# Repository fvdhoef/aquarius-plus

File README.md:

**Next-generation Z80-based retro computer system**

## Documentation

For documentation, please take a look at the [Wiki](https://github.com/fvdhoef/aquarius-plus/wiki).

## Abstract:

What would the Aquarius have evolved into if Mattel hadn't abandoned the system back in 1984? The Aquarius+ is the next-generation of Z80-based 8-bit hardware for the Aquarius platform. The intent is to deliver a cost-effective, backwards-compatible retro computer system that both developers and nostalgists will love and use, all in the spirit of the original, orphaned Aquarius platform.

## Features:

- Backward compatibility with existing Aquarius hardware and software
- Modern, flexible video solution that supports bitmapped graphics, sprites, and tiles, delivered through clean VGA output
- Dual AY sound chips (virtual) for six sound voices
- 512kb of paged RAM in four 16k banks
- Reworked SYSROM and programmable CHARROM
- Integrated SD card and commands (remove dependency on cassette loading)
- WiFi connectivity
- Bluetooth connectivity for modern game controllers

## Folder structure

| Directory           | Description                                                                                                                                                                     |
| ------------------- | ------------------------------------------------------------------------------------------------------------------------------------------------------------------------------- |
| [EndUser](EndUser/) | These files are meant for the normal end-user, that just wants to play and work with the system. You can find some nice sample programs, games and music to run on system here. |
| [Maker](Maker/)     | Files required for makers to manufacture and assemble an Aquarius+ system.                                                                                                      |
| [SDK](SDK/)         | If you want to develop your own software for the Aquarius+, look here.                                                                                                          |
| [System](System/)   | This contains all other files related to the system, including: Schematics/PCB, FPGA, ESP32, Emulator                                                                           |

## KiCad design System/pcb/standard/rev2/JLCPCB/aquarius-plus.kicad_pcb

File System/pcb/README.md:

# Aquarius<sup>+</sup> PCBs
Development of PCBs (Printed Circuit Boards) for the **Aquarius<sup>+</sup>** platform

## Introduction
The **Aquarius<sup>+</sup>** was developed as an open-source platform, including the hardware that comprises the system. To accomplish this and to make tools for the development and manufacture of the platform as accessible as possible, [KiCAD](https://github.com/KiCad/kicad-source-mirror) is used for PCB development, as it is a free, open source tool that has anyone can learn and use.

## Releases
Releases from this repo are by model/PCB and are geared specifically for manufacturing rather than PCB development.

> For example, if you want to make your own **Aquarius<sup>+</sup> Mini**, you would go to the [**Releases**](https://github.com/1stage/aquarius-plus-pcbs/releases) section, find the newest release for an **Aquarius<sup>+</sup> Mini**, and download it.

The **Source code (zip)** or **Source code (tar.gz)** payload will consist of the following components:
 * Gerber files, compressed in ZIP format (includes PCB, Drill, and Map files)
 * PDFs of the SCHEMATIC and PCB
 * BOM (Bill of Materials) and CPL1 (Component Placement Layout) files in XLSX (MS Excel) format, organized for JLCPCB manufacturing.
 * Release notes and other instructions in TXT format

## Development
If you want to explore how the **Aquarius<sup>+</sup>** is designed using KiCAD, you will need to Clone or Fork this repo to your local system. From there you can review and experiment with the schematic, PCB, and other files within the KiCAD environment.

****

## PCB Manufacturing

### PCB Terms
 - BOM - Bill of Materials
 - CPL - Component Placement Layout/List (sometimes referred to as CPL1)
 - PCB - Printed Circuit Board
 - SMT - Surface mount (sometimes referred to as SMD)
 - THT - Through hole

### Process
This guide assumes that the maker will be having a third-party manufacturer create and assemble the PCB. It does not cover user-manufactered PCBs or assembly using a reflow oven or other manual tasks.

#### **JLCPCB** (Cheapest)
1. **Order the parts**
    - On the [JLCPCB](https://jlcpcb.com) main site, log in and go to Parts Manager, then Order Parts, then JLCPCB Parts.
    - From the JLCPCB Assembly Parts page, select BOM Tool.
    - Upload the BOM file to the site. From the pop-up, select the number of PCBs you want to manufacture. This multiplies the quantities for you for each item.
    - Add to cart, pay for items, and wait.
    - Over the next several days, you will get email notifications as items arrive into your parts inventory. Sometimes, there will be an increase or decrease in the amount you paid, so JLCPCB will either ask you to pay the difference (part is more expensive than estimated) or they will credit your purchase (part was less expensive than estimated). Acknowledge these messages, pay the difference (as needed), and wait.
    - Once all of the parts are in your inventory, proceed to the next step.
3. **Order the assembled PCB**
    - Log into JLCPCB, and start a new order.
    - Upload the Gerber files.
    - Mark the order as SMT Assembly.
    - Upload the BOM and CPL files.
    - Ensure there are sufficient quantities of the parts you need. If not, go back to [Order the parts](#JLCPCB) section.
    - Review the placement of all parts. Note that some of the items (ESP32, switch) don't have a 3D model to go with their part, so a small 2x2 checkerboard is used. Don't worry about these items. The CPL1 file has been tuned to accurately place the components, so this step is for QA to make sure nothing has gone wrong.
      - If you select a part (blue highlight), you can nudge it with the arrow keys. RIGHT nudges increase the X. LEFT nudges decrease the X. UP nudges increase the Y. DOWN nudges decrease the Y.
      - For THT parts, it's easier to align the parts from the BOTTOM view, but remember that your X axis is now flipped, so a RIGHT nudge decreases the X and a LEFT nudge increases it.
      - Each "nudge" is a difference of 0.0635mm, and can be added or subtracted from the CPL file accordingly... i.e. if you nudge a part UP (increase y axis) five times, you're modifying it 5 x 0.0635mm or 3.175. So if it's value in the CPL file is -45.025, the new value should be -44.7075.
    - JLCPCB will automatically set the "confirm PCB" and "confirm placement" options, and let you know that there will be a small charge for this.
    - Add to cart, pay for items, and wait.
    - You will get at least two emails. The first will be to confirm your PCB file. This is done in your Order History window. Confirm it. The second email will be to confirm the layout of the components. In your Order History window, the lower Confirm Placement button brings a pop-up which shows the placement of the SMT parts (THT or throughhole is done separately). Everything should be fine, but reply to the email and ask to see a 3D of the cartridge port placement. This will take a day or so, but so long as the port is shown in the far right columns of pins, you can confirm placement.
    - Check the progress of your order daily to make sure there's nothing you need to confirm. Once the product has shipped, you can move onto Assembly.

#### **PCBWay** (PROCESS IN DEVELOPMENT)
1. **Order the assembled PCBs**
    - Visit the PCBWay Aquarius+ Shared Project page for the version you want to manufacture.
	    - [Aquarius+ Standard](https://www.pcbway.com/project/shareproject/Aquarius_Computer_Standard_PCB_0087c6b7.html) 
		- Aquarius+ Mini (coming soon)
	- Click on each of the following buttons to download the manufacturing files:
		- BOM(Bill of materials) - AQP_xxx_BOM_PCBWay_PCBWay Community.xlsx
		- Centroid file - AQP_xxx_CPL1_PCBWay_PCBWay Community.xlsx
		- The xxx in these filenames will be either STD or MINI, depending on the version.
	- Select **PCB+Assembly** and click **Add to Cart**
	- On the Order Page, in the PCB Specification Selection area, confirm the following selections (recommended):
		- Quantity (single): 5 pcs (this is the minimum order of PCBs, but they don't all have to be assembled, and you may have spares if not all are assembled)
		- Solder mask: Blue
		- Remove product No.: Yes (extra+$ 1.5)
		- All other defaults are fine
	- Click on the Assembly Service checkbox to expand/activate it, and confirm the following selections (recommended):
		- 3 flexible options: Turnkey
		- Quantity: 1 pcs (1 is the minimum assembled quantity; you can assemble up to 5 pcs without increasing the number of PCBs above)
		- Copy and paste the contents of the "Mfg_Assembly_Notes_PCBWay.txt" file into the Detailed information of assembly: field.
		- All other defaults are fine
	- Save to Cart
	- In the Cart, under the "Assembly for PCB" section, click on the blue Add File icon to add these files to the Assembly order (you downloaded them above:
		- Click the Parts List (BOM) Upload button and attach  AQP_xxx_BOM_PCBWay_PCBWay Community.xlsx
		- Click the Upload Centroid file and attach AQP_xxx_CPL1_PCBWay_PCBWay Community.xlsx
		- The xxx in these filenames will be either STD or MINI, depending on the version.
		- Click Submit Order now button.
	- You will wait up to a day or so for the files to be reviewed and approved, and a Quote issued.
	- Once you've been approved, return to your Cart and click Proceed to Checkout to pay the amount due
	- Over the next day or two, check your email and answer any questions they might have. 
2. **Wait for about 30 days** (seriously).
3. **Approve final assembly**
	- Reply to the email that will be sent for you to visually inspect/approve parts placement for the board(s), approving the continuation of manufacturing.
	- You will receive shipping confirmation after the boards are completed. Note that for larger orders, you MAY have to pay additional import taxes.
4. **Receive and verify PCBs**
	- You should visually inspect the PCBs once you get them. Make sure all parts are properly installed and soldered in place.
	- Continue onto the Assembly section below.

#### Assembling the Aquarius+
 - Make sure your shipment package has no obvious damage. If it does, take pictures before you open the box and save them for later. Most of the time, a ding or puncture will not be a problem, as the contents are typically very well wrapped.
 - There are sometimes small beads or blobs of solder that get deposited on the top of the board. With a magnifier, check ALL components to ensure there are no obvious solder blobs or bridges on the components, both SMT and THT. Now, check the BACK side of the board to ensure all THT components have solid, well-tented solder joints. Check the metal shrouds around the USB, controllers (DB9), VGA, power switch, and SD card socket to remove any accidental blobs or splashes. They should pop free with minimal force.
 - To assist in the SMT mounting process, manufacturers add additional "rails" to the PCB for handling. Using a small pair of needle-nose pliers, carefully remove these rails by bending along the V cut that has been cut into the PCB next to these rails. Be cautious not to damage any components that rest on this rail (LED, SD card socket, etc.). You can use a small file to remove any remaining burrs along these new edges. The rails can be thrown away.
 -  The wave solder that is used for the THT components leaves a sticky residue, as does the flux used for the SMT components. This residue should be cleaned using a two-step process, first with an alcohol-based solvent and a soft-bristle brush (an old toothbrush works great), and second with a mild de-greasing detergent, also agitated with a soft-bristle brush. Clean BOTH sides of the PCB thoroughly, first with the alcohol (I use left-over hand sanitizer from COVID), and then with the detergent (I use Krud Kutter), rinsing with water after each scrub down. Take care around delicate parts: the goal is to remove residue, not PCB components. Afterwards, either allow to air dry for 24 hours, or use a gentle, low-pressure compressed air source to drive the remaining water from all areas of the PCB (ports, power switch, under chips), again, taking care to not damage PCB components.
 - Once PCB has been cleaned and thoroughly dried, it's time to program the initial image for the Aquarius+. You're programming the ESP32 with the image that then gets sent to the Spartan 6 FPGA. From the GitHub, download the newest AquariusPlus-Firmware-xxx.zip bundle, decompress it, and follow the instructions for setting up the ESP software on your system. Using a USB to USB Micro cable and three 0.1" / 2.54mm pitch jumpers, connect the pins at JP1, JP2, and JP3, and plug the cable into the Aquarius+ power port and into your computer. Switch on the Aquarius+ power supply and note which COM port it appears on.

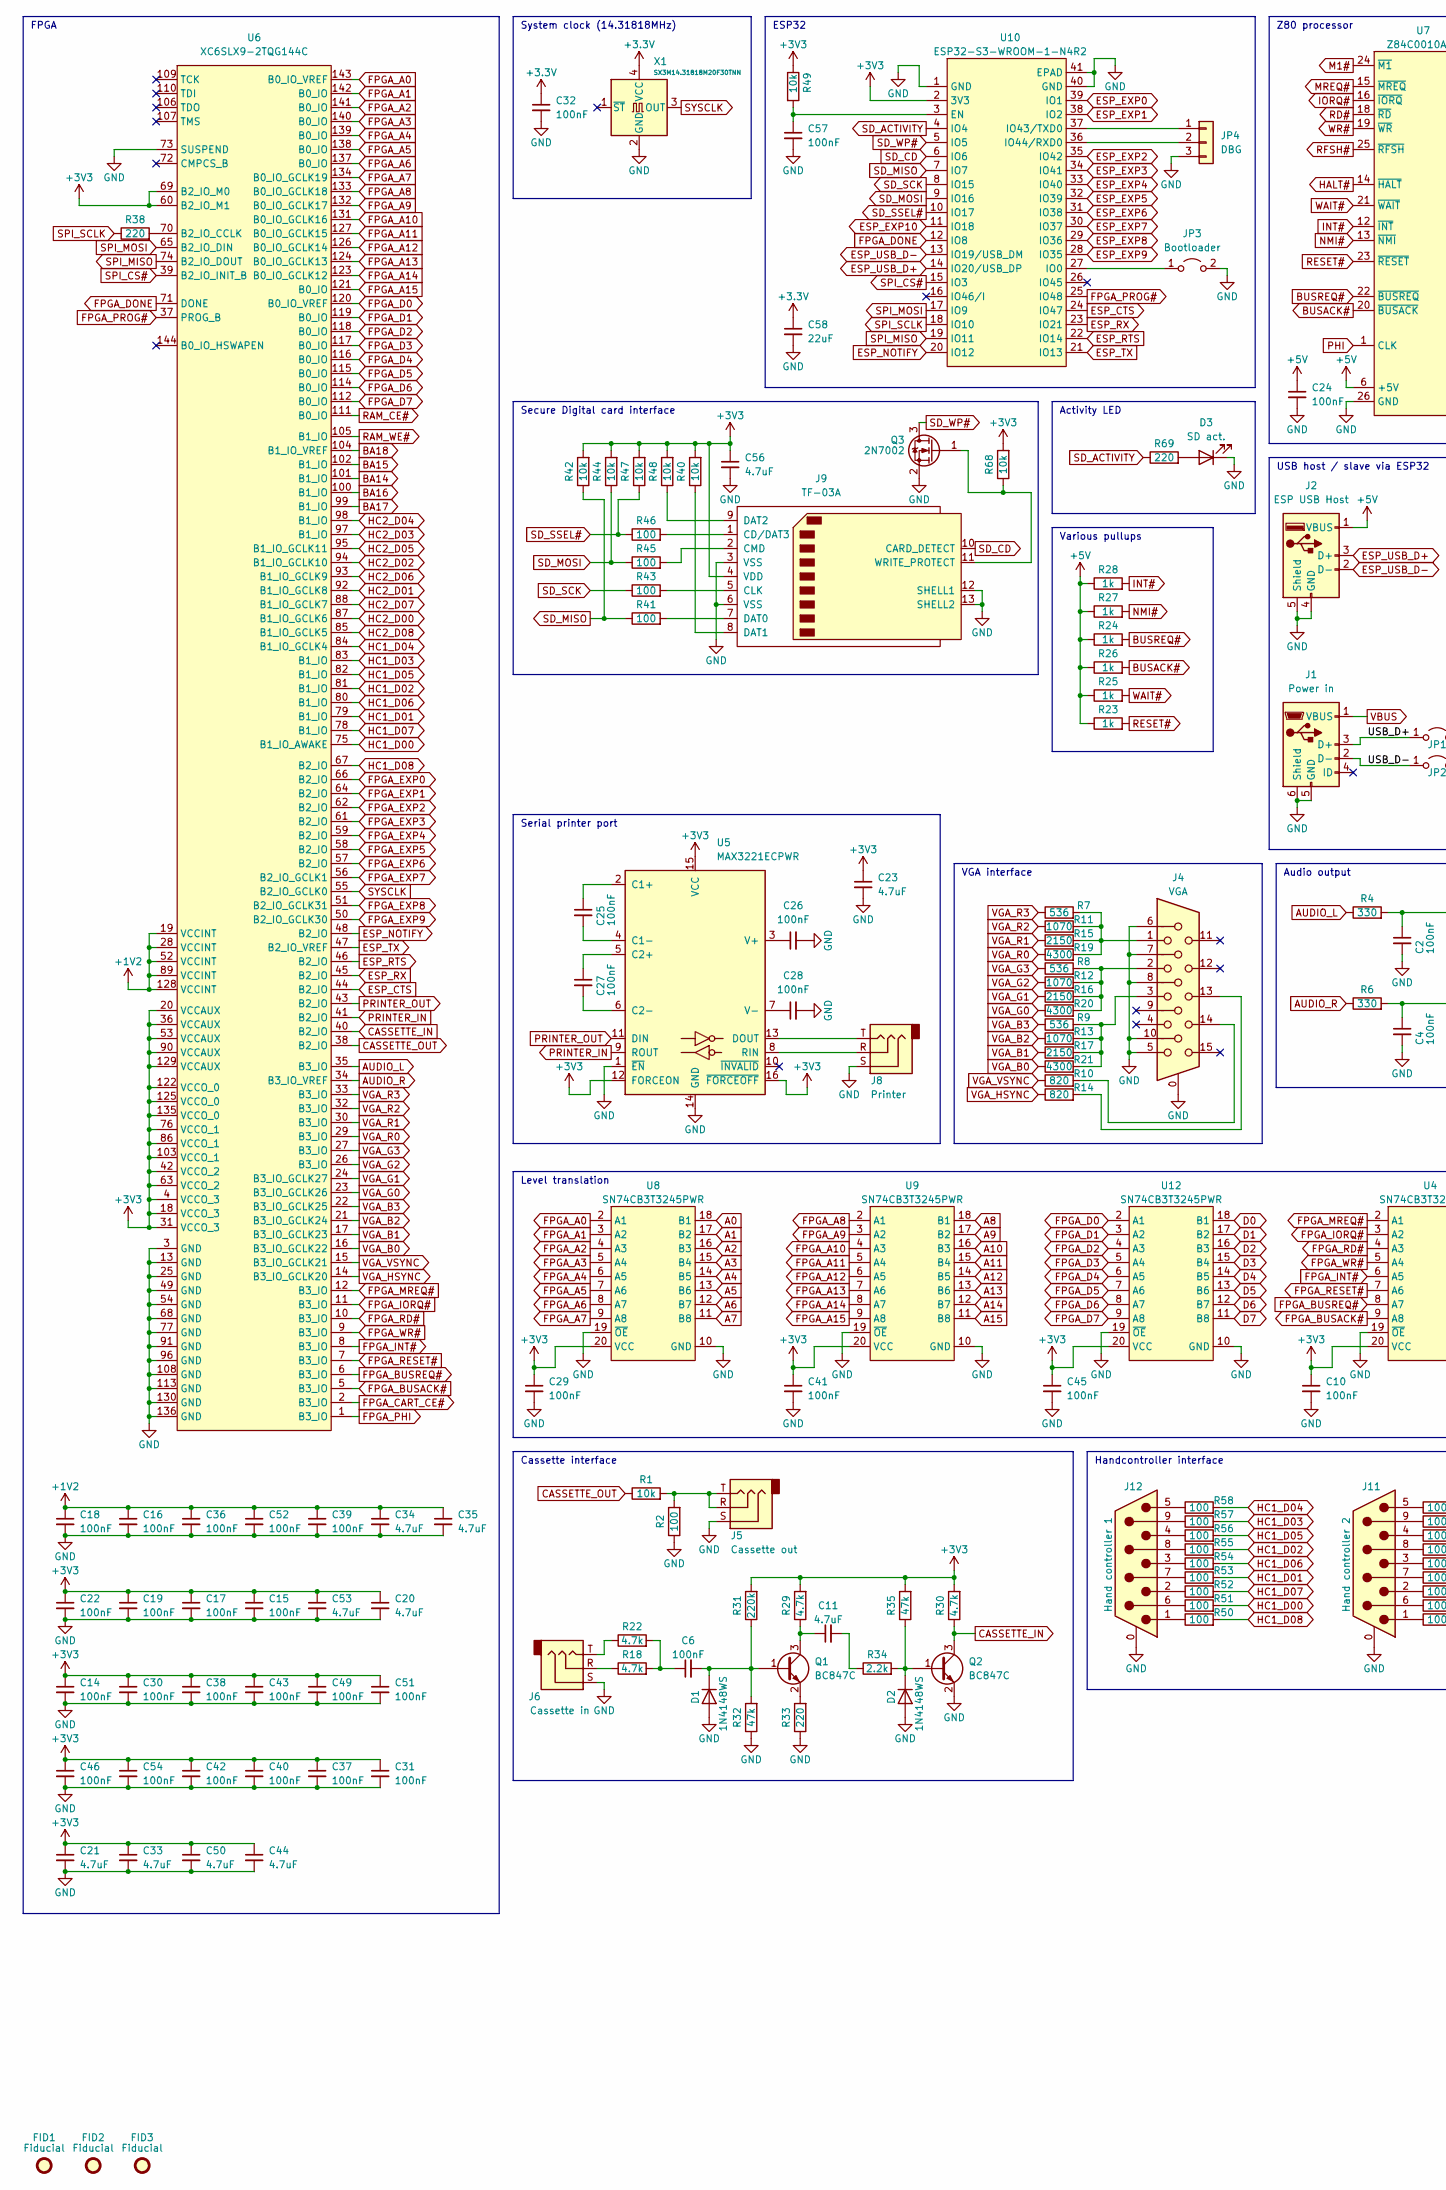
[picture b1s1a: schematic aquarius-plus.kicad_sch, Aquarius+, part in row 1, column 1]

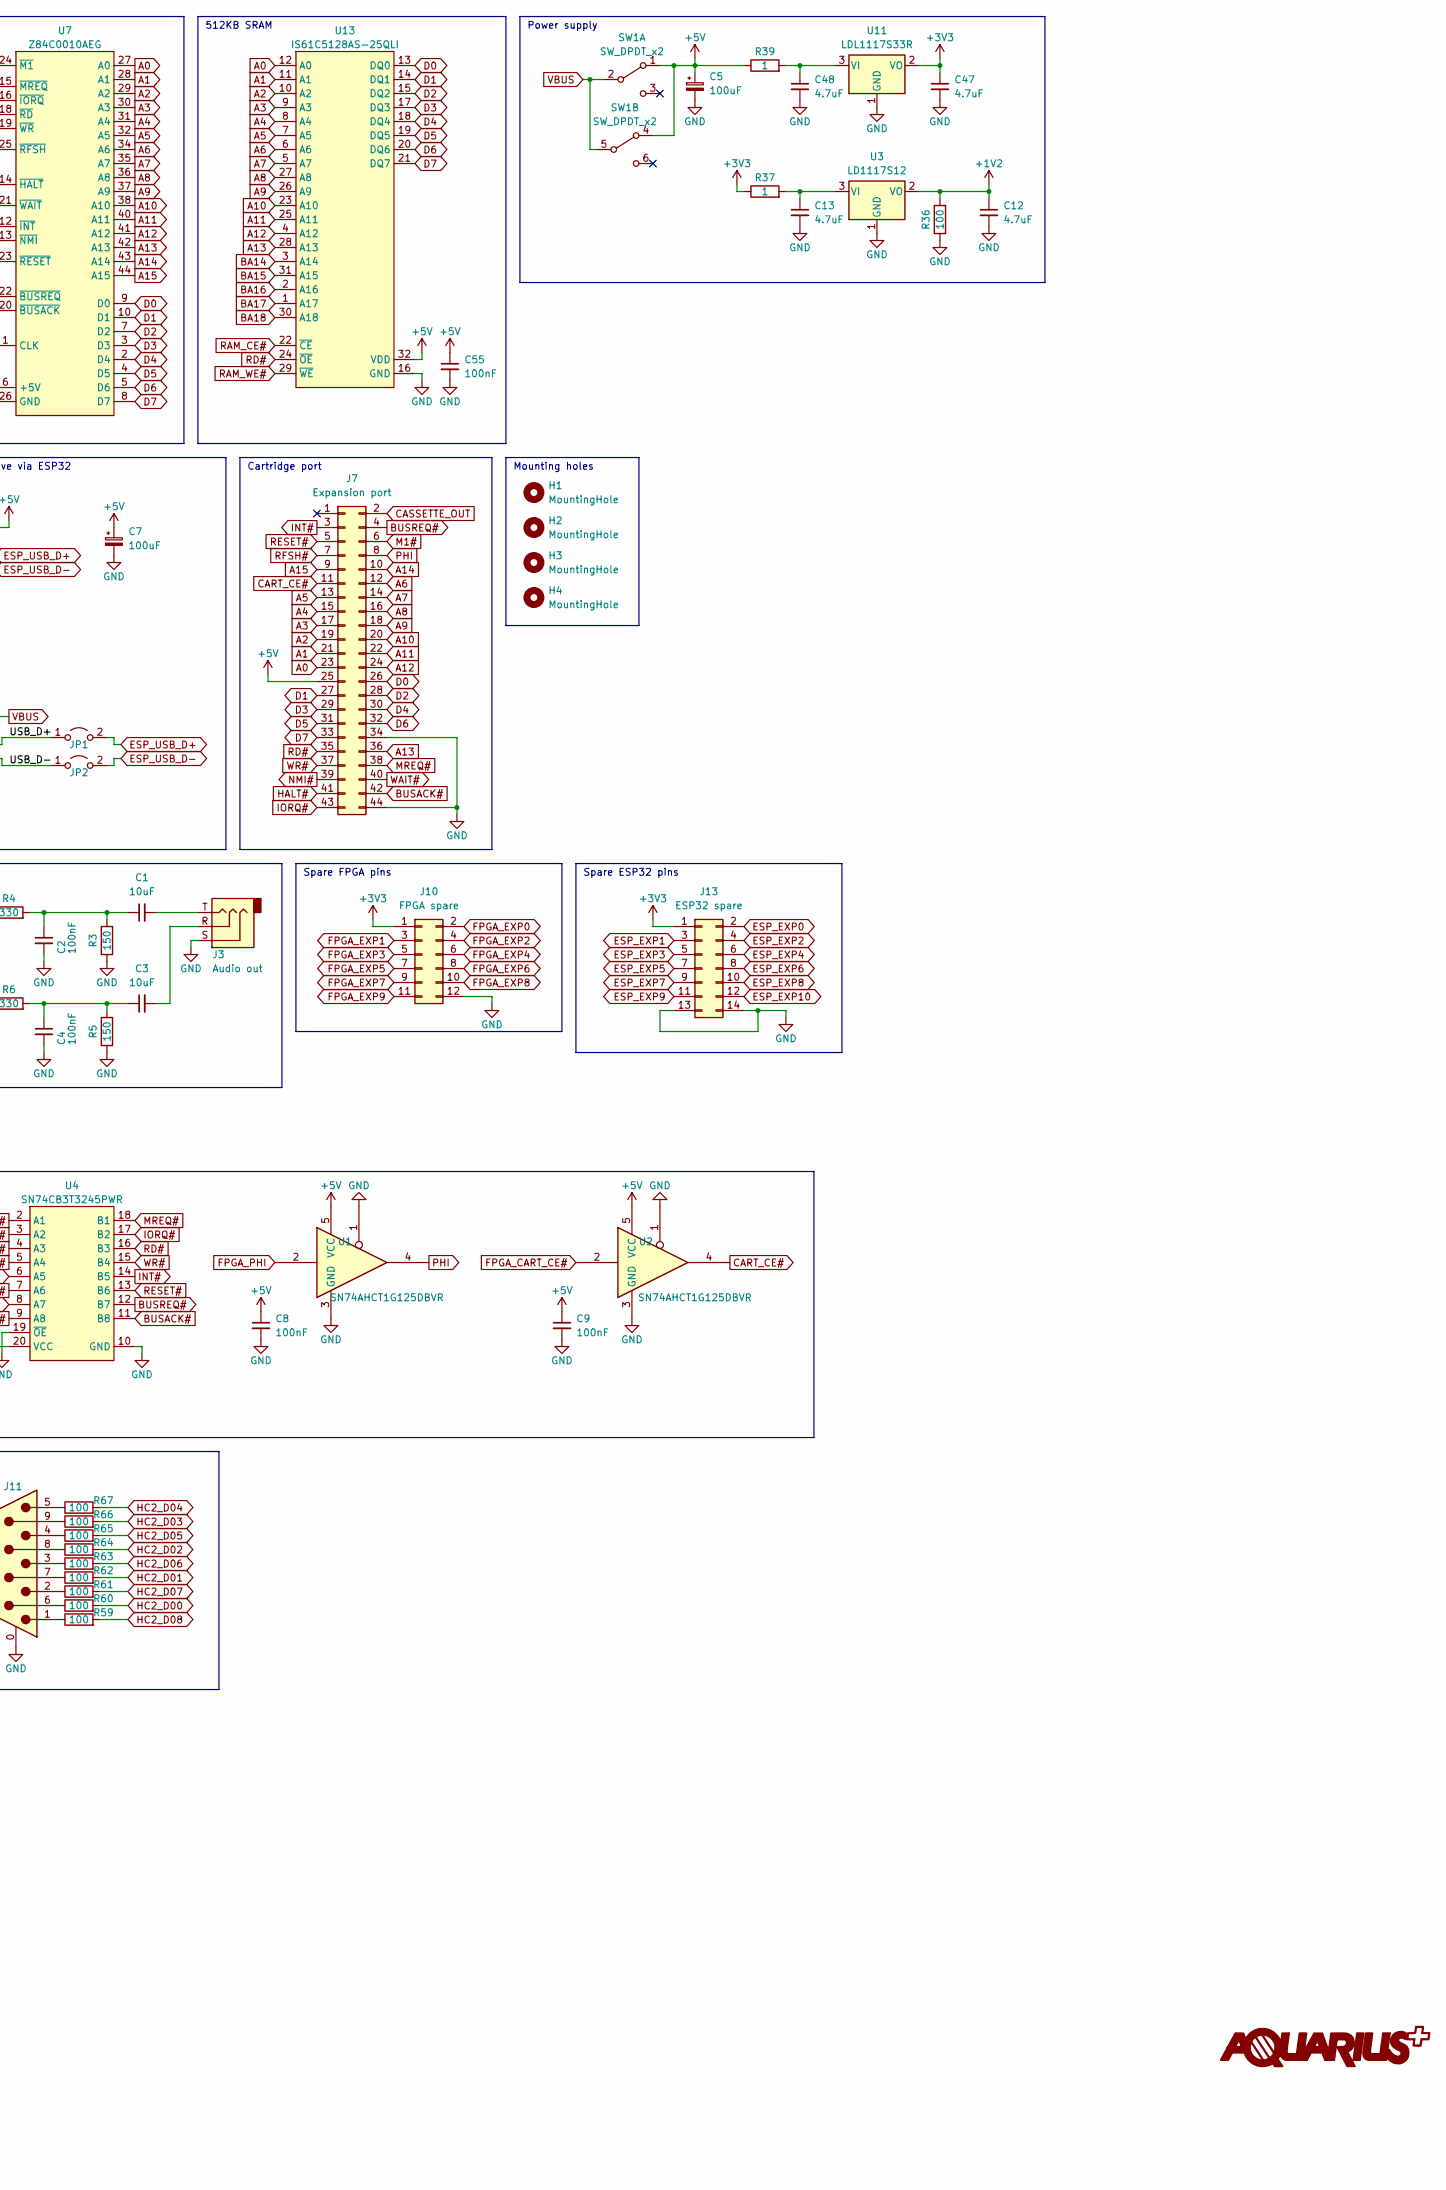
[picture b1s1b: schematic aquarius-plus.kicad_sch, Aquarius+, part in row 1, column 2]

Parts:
C1, C3: 10uF; C_0805_2012Metric
C2, C4, C6, C8, C9, C10, C14, C15, C16, C17, C18, C19, C22, C24, C25, C26, C27, C28, C29, C30, C31, C32, C36, C37, C38, C39, C40, C41, C42, C43, C45, C46, C49, C51, C52, C54, C55, C57: 100nF; C_0603_1608Metric
C5, C7: 100uF; CP_Elec_6.3x7.7
C11, C12, C13, C20, C21, C23, C33, C34, C35, C44, C47, C48, C50, C53, C56: 4.7uF; C_0603_1608Metric
C58: 22uF; C_1206_3216Metric
D1, D2: 1N4148WS; D_SOD-323_HandSoldering
D3: SD act.; LED_D3.0mm_Horizontal_O1.27mm_Z2.0mm
FID1, FID2, FID3: Fiducial; Fiducial_1mm_Mask2mm
H1, H2, H3, H4: MountingHole; MountingHole_3.2mm_M3
J1: Power in; AMPHENOL_10118194-0001LF
J2: ESP USB Host; USB_A_Molex_67643_Horizontal
J3: Audio out; C2939180
J4: VGA; ICD15S13E4GV00LF
J5: Cassette out; C2939180
J6: Cassette in; C2939180
J7: Expansion port; CR22A-44D-2.54DSA(70)
J8: Printer; C2939180
J9: TF-03A
J10: FPGA spare; PinHeader_2x06_P2.54mm_Vertical
J11: Hand controller 2; DSUB-9_Male_Horizontal_P2.77x2.84mm_EdgePinOffset9.90mm_Hou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
J12: Hand controller 1; DSUB-9_Male_Horizontal_P2.77x2.84mm_EdgePinOffset9.90mm_Hou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
J13: ESP32 spare; PinHeader_2x07_P2.54mm_Vertical
JP1, JP2: USB; PinHeader_1x02_P2.54mm_Vertical
JP3: Bootloader; PinHeader_1x02_P2.54mm_Vertical
JP4: DBG; PinHeader_1x03_P2.54mm_Vertical
Q1, Q2: BC847C; SOT-23
Q3: 2N7002; SOT-23
R1, R40, R42, R44, R47, R48, R49, R68: 10k; R_0603_1608Metric
R2, R36, R41, R43, R45, R46, R50, R51, R52, R53, R54, R55, R56, R57, R58, R59, R60, R61, R62, R63, R64, R65, R66, R67: 100; R_0603_1608Metric
R3, R5: 150; R_0603_1608Metric
R4, R6: 330; R_0603_1608Metric
R7, R8, R9: 536; R_0603_1608Metric
R10, R14: 820; R_0603_1608Metric
R11, R12, R13: 1070; R_0603_1608Metric
R15, R16, R17: 2150; R_0603_1608Metric
R18, R22, R29, R30: 4.7k; R_0603_1608Metric
R19, R20, R21: 4300; R_0603_1608Metric
R23, R24, R25, R26, R27, R28: 1k; R_0603_1608Metric
R31: 220k; R_0603_1608Metric
R32, R35: 47k; R_0603_1608Metric
R33, R38, R69: 220; R_0603_1608Metric
R34: 2.2k; R_0603_1608Metric
R37, R39: 1; R_0603_1608Metric
SW1: SW_DPDT_x2; SW_E-Switch_EG2219_DPDT_Angled
U1, U2: SN74AHCT1G125DBVR; SOT-23-5
U3: LD1117S12; SOT-223-3_TabPin2
U4, U8, U9, U12: SN74CB3T3245PWR; TSSOP-20_4.4x6.5mm_P0.65mm
U5: MAX3221ECPWR; TSSOP-16_4.4x5mm_P0.65mm
U6: XC6SLX9-2TQG144C; TQFP-144_20x20mm_P0.5mm
U7: Z84C0010AEG; LQFP-44_10x10mm_P0.8mm
U10: ESP32-S3-WROOM-1-N4R2; ESP32-S2-SOLO-N4R2
U11: LDL1117S33R; SOT-223-3_TabPin2
U13: IS61C5128AS-25QLI; SSOP-32_11.305x20.495mm_P1.27mm
X1: SX3M14.31818M20F30TNN; Oscillator_SMD_SeikoEpson_SG8002CE-4Pin_3.2x2.5mm

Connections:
+1V2: C12.1, C16.1, C18.1, C34.1, C35.1, C36.1, C39.1, C52.1, R36.2, U3.2 (VO), U6.19 (VCCINT), U6.28 (VCCINT), U6.52 (VCCINT), U6.89 (VCCINT), U6.128 (VCCINT)
+5V: C5.1, C7.1, C8.1, C9.1, C24.1, C55.1, J2.1 (VBUS), J7.25, R23.1, R24.1, R25.1, R26.1, R27.1, R28.1, R39.1, SW1.1 (A), SW1.4 (A), U1.5 (VCC), U2.5 (VCC), U7.6 (+5V), U13.32 (VDD)
/USB_D+: J1.3 (D+), JP1.1 (A)
/USB_D-: J1.2 (D-), JP2.1 (A)
A0: J7.23, U7.27 (A0), U8.18 (B1), U13.12 (A0)
A1: J7.21, U7.28 (A1), U8.17 (B2), U13.11 (A1)
A2: J7.19, U7.29 (A2), U8.16 (B3), U13.10 (A2)
A3: J7.17, U7.30 (A3), U8.15 (B4), U13.9 (A3)
A4: J7.15, U7.31 (A4), U8.14 (B5), U13.8 (A4)
A5: J7.13, U7.32 (A5), U8.13 (B6), U13.7 (A5)
A6: J7.12, U7.34 (A6), U8.12 (B7), U13.6 (A6)
A7: J7.14, U7.35 (A7), U8.11 (B8), U13.5 (A7)
A8: J7.16, U7.36 (A8), U9.18 (B1), U13.27 (A8)
A9: J7.18, U7.37 (A9), U9.17 (B2), U13.26 (A9)
A10: J7.20, U7.38 (A10), U9.16 (B3), U13.23 (A10)
A11: J7.22, U7.40 (A11), U9.15 (B4), U13.25 (A11)
A12: J7.24, U7.41 (A12), U9.14 (B5), U13.4 (A12)
A13: J7.36, U7.42 (A13), U9.13 (B6), U13.28 (A13)
A14: J7.10, U7.43 (A14), U9.12 (B7)
A15: J7.9, U7.44 (A15), U9.11 (B8)
AUDIO_L: R4.1, U6.35 (B3_IO)
AUDIO_R: R6.1, U6.34 (B3_IO_VREF)
BA14: U6.101 (B1_IO), U13.3 (A14)
BA15: U6.102 (B1_IO), U13.31 (A15)
BA16: U6.100 (B1_IO), U13.2 (A16)
BA17: U6.99 (B1_IO), U13.1 (A17)
BA18: U6.104 (B1_IO_VREF), U13.30 (A18)
BUSACK#: J7.42, R26.2, U4.11 (B8), U7.20 (~BUSACK)
BUSREQ#: J7.4, R24.2, U4.12 (B7), U7.22 (~BUSREQ)
CART_CE#: J7.11, U2.4
CASSETTE_IN: Q2.3 (C), R30.1, U6.40 (B2_IO)
CASSETTE_OUT: J7.2, R1.1, U6.38 (B2_IO)
D0: J7.26, U7.9 (D0), U12.18 (B1), U13.13 (DQ0)
D1: J7.27, U7.10 (D1), U12.17 (B2), U13.14 (DQ1)
D2: J7.28, U7.7 (D2), U12.16 (B3), U13.15 (DQ2)
D3: J7.29, U7.3 (D3), U12.15 (B4), U13.17 (DQ3)
D4: J7.30, U7.2 (D4), U12.14 (B5), U13.18 (DQ4)
D5: J7.31, U7.4 (D5), U12.13 (B6), U13.19 (DQ5)
D6: J7.32, U7.5 (D6), U12.12 (B7), U13.20 (DQ6)
D7: J7.33, U7.8 (D7), U12.11 (B8), U13.21 (DQ7)
ESP_CTS: U6.44 (B2_IO), U10.24 (IO47)
ESP_EXP0: J13.2, U10.39 (IO1)
ESP_EXP1: J13.3, U10.38 (IO2)
ESP_EXP2: J13.4, U10.35 (IO42)
ESP_EXP3: J13.5, U10.34 (IO41)
ESP_EXP4: J13.6, U10.33 (IO40)
ESP_EXP5: J13.7, U10.32 (IO39)
ESP_EXP6: J13.8, U10.31 (IO38)
ESP_EXP7: J13.9, U10.30 (IO37)
ESP_EXP8: J13.10, U10.29 (IO36)
ESP_EXP9: J13.11, U10.28 (IO35)
ESP_EXP10: J13.12, U10.11 (IO18)
ESP_NOTIFY: U6.48 (B2_IO), U10.20 (IO12)
ESP_RTS: U6.46 (B2_IO), U10.22 (IO14)
ESP_RX: U6.45 (B2_IO), U10.23 (IO21)
ESP_TX: U6.47 (B2_IO_VREF), U10.21 (IO13)
ESP_USB_D+: J2.3 (D+), JP1.2 (B), U10.14 (IO20/USB_DP)
ESP_USB_D-: J2.2 (D-), JP2.2 (B), U10.13 (IO19/USB_DM)
FPGA_A0: U6.143 (B0_IO_VREF), U8.2 (A1)
FPGA_A1: U6.142 (B0_IO), U8.3 (A2)
FPGA_A2: U6.141 (B0_IO), U8.4 (A3)
FPGA_A3: U6.140 (B0_IO), U8.5 (A4)
FPGA_A4: U6.139 (B0_IO), U8.6 (A5)
FPGA_A5: U6.138 (B0_IO), U8.7 (A6)
FPGA_A6: U6.137 (B0_IO), U8.8 (A7)
FPGA_A7: U6.134 (B0_IO_GCLK19), U8.9 (A8)
FPGA_A8: U6.133 (B0_IO_GCLK18), U9.2 (A1)
FPGA_A9: U6.132 (B0_IO_GCLK17), U9.3 (A2)
FPGA_A10: U6.131 (B0_IO_GCLK16), U9.4 (A3)
FPGA_A11: U6.127 (B0_IO_GCLK15), U9.5 (A4)
FPGA_A12: U6.126 (B0_IO_GCLK14), U9.6 (A5)
FPGA_A13: U6.124 (B0_IO_GCLK13), U9.7 (A6)
FPGA_A14: U6.123 (B0_IO_GCLK12), U9.8 (A7)
FPGA_A15: U6.121 (B0_IO), U9.9 (A8)
FPGA_BUSACK#: U4.9 (A8), U6.5 (B3_IO)
FPGA_BUSREQ#: U4.8 (A7), U6.6 (B3_IO)
FPGA_CART_CE#: U2.2, U6.2 (B3_IO)
FPGA_D0: U6.120 (B0_IO_VREF), U12.2 (A1)
FPGA_D1: U6.119 (B0_IO), U12.3 (A2)
FPGA_D2: U6.118 (B0_IO), U12.4 (A3)
FPGA_D3: U6.117 (B0_IO), U12.5 (A4)
FPGA_D4: U6.116 (B0_IO), U12.6 (A5)
FPGA_D5: U6.115 (B0_IO), U12.7 (A6)
FPGA_D6: U6.114 (B0_IO), U12.8 (A7)
FPGA_D7: U6.112 (B0_IO), U12.9 (A8)
FPGA_DONE: U6.71 (DONE), U10.12 (IO8)
FPGA_EXP0: J10.2, U6.66 (B2_IO)
FPGA_EXP1: J10.3, U6.64 (B2_IO)
FPGA_EXP2: J10.4, U6.62 (B2_IO)
FPGA_EXP3: J10.5, U6.61 (B2_IO)
FPGA_EXP4: J10.6, U6.59 (B2_IO)
FPGA_EXP5: J10.7, U6.58 (B2_IO)
FPGA_EXP6: J10.8, U6.57 (B2_IO)
FPGA_EXP7: J10.9, U6.56 (B2_IO_GCLK1)
FPGA_EXP8: J10.10, U6.51 (B2_IO_GCLK31)
FPGA_EXP9: J10.11, U6.50 (B2_IO_GCLK30)
FPGA_INT#: U4.6 (A5), U6.8 (B3_IO)
FPGA_IORQ#: U4.3 (A2), U6.11 (B3_IO)
FPGA_MREQ#: U4.2 (A1), U6.12 (B3_IO)
FPGA_PHI: U1.2, U6.1 (B3_IO)
FPGA_PROG#: U6.37 (PROG_B), U10.25 (IO48)
FPGA_RD#: U4.4 (A3), U6.10 (B3_IO)
FPGA_RESET#: U4.7 (A6), U6.7 (B3_IO)
FPGA_WR#: U4.5 (A4), U6.9 (B3_IO)
GND: C2.2, C4.2, C5.2, C7.2, C8.2, C9.2, C10.2, C12.2, C13.2, C14.2, C15.2, C16.2, C17.2, C18.2, C19.2, C20.2, C21.2, C22.2, C23.2, C24.2, C26.2, C28.2, C29.2, C30.2, C31.2, C32.2, C33.2, C34.2, C35.2, C36.2, C37.2, C38.2, C39.2, C40.2, C41.2, C42.2, C43.2, C44.2, C45.2, C46.2, C47.2, C48.2, C49.2, C50.2, C51.2, C52.2, C53.2, C54.2, C55.2, C56.2, C57.2, C58.2, D1.2 (A), D2.2 (A), D3.1 (K), J1.5 (GND), J1.6 (Shield), J2.4 (GND), J2.5 (Shield), J3.S, J4.0, J4.5, J4.6, J4.7, J4.8, J4.10, J5.S, J6.S, J7.34, J7.44, J8.S, J9.3 (VSS), J9.6 (VSS), J9.12 (SHELL1), J9.13 (SHELL2), J10.12, J11.0 (PAD), J12.0 (PAD), J13.13, J13.14, JP3.2 (B), JP4.3, Q2.2 (E), Q3.2 (S), R2.1, R3.1, R5.1, R32.1, R33.1, R36.1, U1.1, U1.3 (GND), U2.1, U2.3 (GND), U3.1 (GND), U4.10 (GND), U4.19 (~OE), U5.1 (~EN), U5.14 (GND), U6.3 (GND), U6.13 (GND), U6.25 (GND), U6.49 (GND), U6.54 (GND), U6.68 (GND), U6.73 (SUSPEND), U6.77 (GND), U6.91 (GND), U6.96 (GND), U6.108 (GND), U6.113 (GND), U6.130 (GND), U6.136 (GND), U7.26 (GND), U8.10 (GND), U8.19 (~OE), U9.10 (GND), U9.19 (~OE), U10.1 (GND), U10.40 (GND), U10.41 (EPAD), U11.1 (GND), U12.10 (GND), U12.19 (~OE), U13.16 (GND), X1.2 (GND)
HALT#: J7.41, U7.14 (~HALT)
HC1_D00: R51.2, U6.75 (B1_IO_AWAKE)
HC1_D01: R53.2, U6.79 (B1_IO)
HC1_D02: R55.2, U6.81 (B1_IO)
HC1_D03: R57.2, U6.83 (B1_IO)
HC1_D04: R58.2, U6.84 (B1_IO_GCLK4)
HC1_D05: R56.2, U6.82 (B1_IO)
HC1_D06: R54.2, U6.80 (B1_IO)
HC1_D07: R52.2, U6.78 (B1_IO)
HC1_D08: R50.2, U6.67 (B2_IO)
HC2_D00: R60.2, U6.87 (B1_IO_GCLK6)
HC2_D01: R62.2, U6.92 (B1_IO_GCLK8)
HC2_D02: R64.2, U6.94 (B1_IO_GCLK10)
HC2_D03: R66.2, U6.97 (B1_IO)
HC2_D04: R67.2, U6.98 (B1_IO)
HC2_D05: R65.2, U6.95 (B1_IO_GCLK11)
HC2_D06: R63.2, U6.93 (B1_IO_GCLK9)
HC2_D07: R61.2, U6.88 (B1_IO_GCLK7)
HC2_D08: R59.2, U6.85 (B1_IO_GCLK5)
INT#: J7.3, R28.2, U4.14 (B5), U7.12 (~INT)
IORQ#: J7.43, U4.17 (B2), U7.16 (~IORQ)
M1#: J7.6, U7.24 (~M1)
MREQ#: J7.38, U4.18 (B1), U7.15 (~MREQ)
NMI#: J7.39, R27.2, U7.13 (~NMI)
unnamed: C1.1, C2.1, R3.2, R4.2
unnamed: C1.2, J3.T
unnamed: C3.1, C4.1, R5.2, R6.2
unnamed: C3.2, J3.R
unnamed: C6.1, R18.2, R22.2
unnamed: C11.2, R34.1
unnamed: C6.2, D1.1 (K), Q1.1 (B), R31.1, R32.2
unnamed: D2.1 (K), Q2.1 (B), R34.2, R35.1
unnamed: D3.2 (A), R69.2
unnamed: J4.1, R7.2, R11.2, R15.2, R19.2
unnamed: J4.2, R8.2, R12.2, R16.2, R20.2
unnamed: J4.3, R9.2, R13.2, R17.2, R21.2
unnamed: J4.13, R14.2
unnamed: J4.14, R10.2
unnamed: J5.R, J5.T, R1.2, R2.2
unnamed: J6.R, R18.1
unnamed: J6.T, R22.1
unnamed: J9.1 (CD/DAT3), R46.2
unnamed: J9.5 (CLK), R43.2
unnamed: J9.2 (CMD), R45.2
unnamed: J9.7 (DAT0), R41.2
unnamed: J9.8 (DAT1), R40.1
unnamed: J9.9 (DAT2), R48.1
unnamed: J9.11 (WRITE_PROTECT), Q3.1 (G), R68.1
unnamed: J11.1, R59.1
unnamed: J11.2, R61.1
unnamed: J11.3, R63.1
unnamed: J11.4, R65.1
unnamed: J11.5, R67.1
unnamed: J11.6, R60.1
unnamed: J11.7, R62.1
unnamed: J11.8, R64.1
unnamed: J11.9, R66.1
unnamed: J12.1, R50.1
unnamed: J12.2, R52.1
unnamed: J12.3, R54.1
unnamed: J12.4, R56.1
unnamed: J12.5, R58.1
unnamed: J12.6, R51.1
unnamed: J12.7, R53.1
unnamed: J12.8, R55.1
unnamed: J12.9, R57.1
unnamed: JP3.1 (A), U10.27 (IO0)
unnamed: JP4.1, U10.37 (IO43/TXD0)
unnamed: JP4.2, U10.36 (IO44/RXD0)
unnamed: C11.1, Q1.3 (C), R29.1
unnamed: Q1.2 (E), R33.2
unnamed: C13.1, R37.2, U3.3 (VI)
unnamed: C25.1, U5.2 (C1+)
unnamed: C25.2, U5.4 (C1-)
unnamed: C27.1, U5.5 (C2+)
unnamed: C27.2, U5.6 (C2-)
unnamed: J8.T, U5.13 (DOUT)
unnamed: J8.R, U5.8 (RIN)
unnamed: C26.1, U5.3 (V+)
unnamed: C28.1, U5.7 (V-)
unnamed: R38.2, U6.70 (B2_IO_CCLK)
unnamed: C57.1, R49.2, U10.3 (EN)
unnamed: C48.1, R39.2, U11.3 (VI)
PHI: J7.8, U1.4, U7.1 (CLK)
PRINTER_IN: U5.9 (ROUT), U6.41 (B2_IO)
PRINTER_OUT: U5.11 (DIN), U6.43 (B2_IO)
RAM_CE#: U6.111 (B0_IO), U13.22 (~CE)
RAM_WE#: U6.105 (B1_IO), U13.29 (~WE)
RD#: J7.35, U4.16 (B3), U7.18 (~RD), U13.24 (~OE)
RESET#: J7.5, R23.2, U4.13 (B6), U7.23 (~RESET)
RFSH#: J7.7, U7.25 (~RFSH)
SD_ACTIVITY: R69.1, U10.4 (IO4)
SD_CD: J9.10 (CARD_DETECT), U10.6 (IO6)
SD_MISO: R41.1, R42.1, U10.7 (IO7)
SD_MOSI: R44.1, R45.1, U10.9 (IO16)
SD_SCK: R43.1, U10.8 (IO15)
SD_SSEL#: R46.1, R47.1, U10.10 (IO17)
SD_WP#: Q3.3 (D), U10.5 (IO5)
SPI_CS#: U6.39 (B2_IO_INIT_B), U10.15 (IO3)
SPI_MISO: U6.74 (B2_IO_DOUT), U10.19 (IO11)
SPI_MOSI: U6.65 (B2_IO_DIN), U10.17 (IO9)
SPI_SCLK: R38.1, U10.18 (IO10)
SYSCLK: U6.55 (B2_IO_GCLK0), X1.3 (OUT)
VBUS: J1.1 (VBUS), SW1.2 (B), SW1.5 (B)
VGA_B0: R21.1, U6.16 (B3_IO_GCLK22)
VGA_B1: R17.1, U6.17 (B3_IO_GCLK23)
VGA_B2: R13.1, U6.21 (B3_IO_GCLK24)
VGA_B3: R9.1, U6.22 (B3_IO_GCLK25)
VGA_G0: R20.1, U6.23 (B3_IO_GCLK26)
VGA_G1: R16.1, U6.24 (B3_IO_GCLK27)
VGA_G2: R12.1, U6.26 (B3_IO)
VGA_G3: R8.1, U6.27 (B3_IO)
VGA_HSYNC: R14.1, U6.14 (B3_IO_GCLK20)
VGA_R0: R19.1, U6.29 (B3_IO)
VGA_R1: R15.1, U6.30 (B3_IO)
VGA_R2: R11.1, U6.32 (B3_IO)
VGA_R3: R7.1, U6.33 (B3_IO)
VGA_VSYNC: R10.1, U6.15 (B3_IO_GCLK21)
WAIT#: J7.40, R25.2, U7.21 (~WAIT)
WR#: J7.37, U4.15 (B4), U7.19 (~WR)

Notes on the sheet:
Level translation
System clock (14.31818MHz)
USB host / slave via ESP32
Various pullups
Audio output
Activity LED
Cartridge port
Serial printer port
Power supply
Spare FPGA pins
Cassette interface
ESP32
512KB SRAM
Z80 processor
FPGA
Spare ESP32 pins
VGA interface
Mounting holes
Secure Digital card interface
Handcontroller interface

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
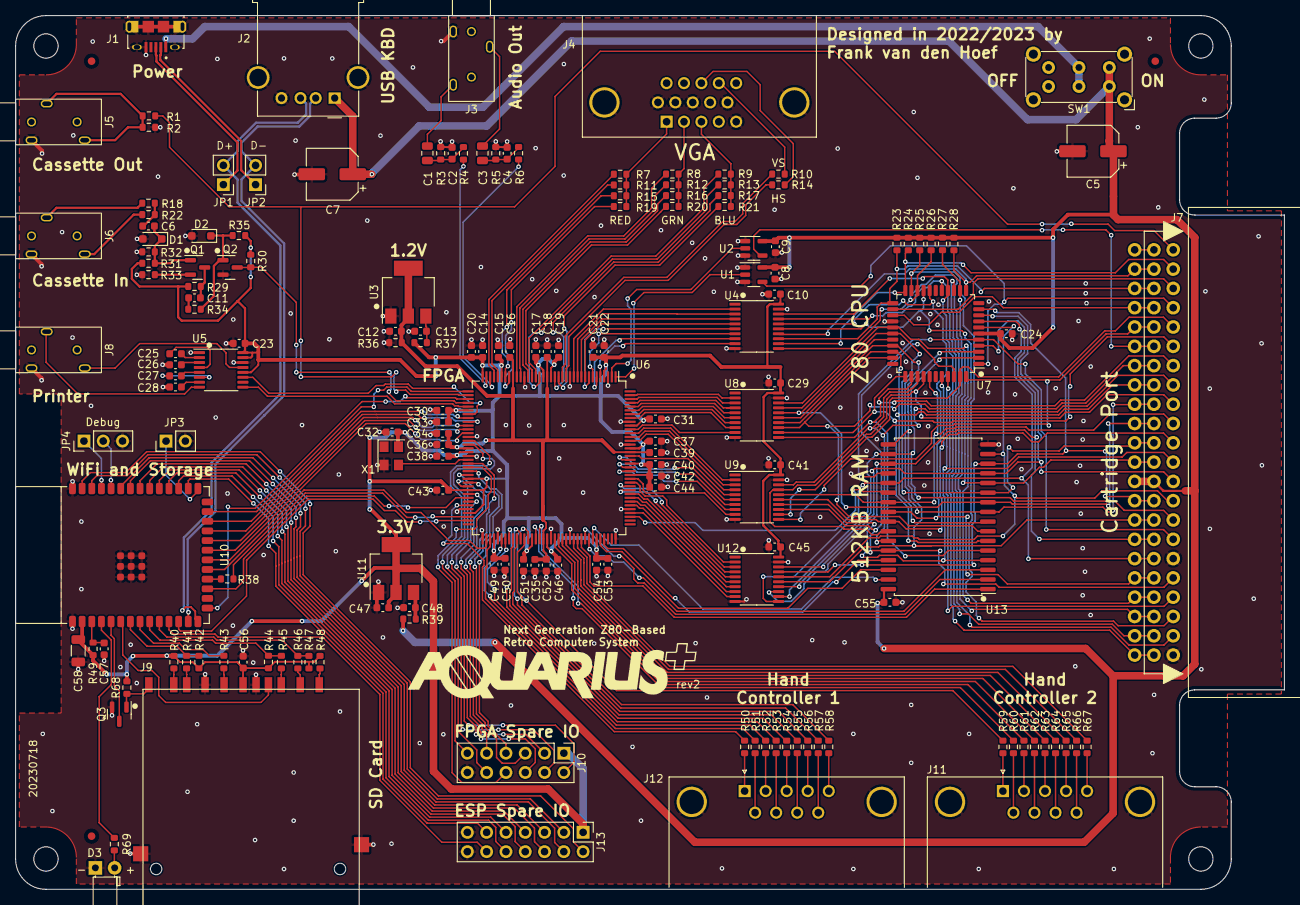
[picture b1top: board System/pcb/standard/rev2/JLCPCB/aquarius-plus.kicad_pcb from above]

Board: 2 copper layers, 167.0 x 115.0 mm, 172 parts (0 on the bottom side), 226 nets.
